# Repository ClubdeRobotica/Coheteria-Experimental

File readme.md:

# Vectores experimentales

## Introducción:
Es un proyecto orientado principalmente al estudio de la construccion de cohetes para el lanzamiento de nano satelites. Como incio del proyecto lo que se busca es generar la tecnologia y documentacion necesaria para poder realizar lanzamientos de cansat ( un pequeño satélite del tamaño de una lata de gaseosa). Por otro lado se busca generar mayor interes en las actividades espaciales que son muy pocas difundidas y asi ayudar con el progreso tecnológico.

## Objetivos

El objetivo principal de este proyecto, es lograr desarrollar un pequeño lanzador, que se pueda replicar facilmente y que sea capaz de llevar un cansat a una altura de unos 500 a 1000 metros.
Dividimos al proyecto en dos fases principales, con la primera nos planteamos generar todas las herramientas necesarias para el desarrollo de cohetes, y en la segunda se comienza a desarrollar cohetes y motores.
Dado que este proyecto está apuntado a ser desarrollado por estudiantes sin niguna experiencia previa en coheteria, se planea generar un entorno de desarrollo completo, para que sea posible evaluar los dferentes diseños, tanto de motores como de cohetes.

## Primera Fase
Para poder resolver todos los problemas que surjan a la hora de armar y lanzar un cohete desde cero, se plantean dos bloques de telemetria:
- Kit de Desarrollo de Motores, compuesto por:
 - Un kit de desarrollo para motores de azucar, que permita medir el empuje generado por las distintos propelentes, para poder experimentar con distintos motores sin necesidad de tener que ir al campo a probarlo en un cohete.
 - Una estacion terrena para el controlador de vuelo, es un software que se conecta al controlador de vuelo y permite descargar todos los datos almacenados durante el vuelo y generar graficos que permitan visualizar mas clararamente los datos.
- Kit de Desarrollo para Cohetes, compuesto por:
 - Controlador de vuelo electrónico, capaz de adquirir todos los datos del vuelo y guardarlos en una memoria para su posterior análisis.
 - Una estacion de control para el banco de pruebas, se trata simplemente de un software capaz de conectarse al banco y desde el cual se puedan visualizar todos los datos generados durante la prueba.

Como un anexo para esta fase, se añade el desarrollo de una plataforma para el lanzamiento de los cohetes.

### Kit de Desarrollo de Motores

El kit de desarrollo para motores de baja potencia, esta compuesto por un sistema mecanico donde se montan los motores y la electrónica necesaria para el analisis del empuje y un sistema informatico para controlar las pruebas. Este kit se encuentra en la etapa final del desarrollo y se puede ver en la [pagina del banco de pruebas](https://github.com/ClubdeRobotica/Coheteria-Experimental/tree/Bayo_V1/Motor/Banco%20de%20pruebas)

#### Sistema mecánico
El sistema mecánico, fabricado con perfiles de aluminio es simplemente una plataforma deslizante y un montaje para una celda de carga. La electronica implicada en este banco es la mas sencilla puesto que se trata simplemente de una placa Wemos D1, con un firmware de arduino que nos permite activar un relay para encender el motor y tomar mediciones de la celda de carga por WiFi.

#### Sistema informático
Está desarrollado en python y ademas de conectarse al banco de pruebas, nos muestra un grafico sencillo de empuje/tiempo.

### Kit de Desarrollo de Cohetes

Se trata como se dijo antes de una placa de telemetria que durante el vuelo va tomando a intervalos regulares, mediciones de presión, temperatura y aceleración y almacenandolos en un archivo que al finalizar el vuelo se puede descargar para su analisis. Adicionalmente se agrega un buzzer, que previo al despegue idica los distintos estados del sistema por medio de distintas combinaciones sonoras y al final del mismo, genera una alarma para facilitar su recuperacion en caso de caer en terreno accidentado.

#### Sistema Electrónico
La placa esta basada en un ESP8266 (en una primera fase en Wemos D1 mini, para simplificar el desarrollo) con un firmware de tiempo real basado en freeRTOS.
Consta de:
- Placa principal: Wemos D1 mini, modificada para mayor alcance del WiFi.
- Sensor de presion y temperatura BMP180
- Acelerómetro de tres ejes ADXL345
- Buzzer
- Bateria de 3.6V

Al iniciar, activa un AP WiFi y un servidor web al que se puede acceder desde una pc, para configurar las condiciones iniciales, o activar el modo de vuelo. Una vez activado el modo de vuelo, el sistema apaga el AP y queda a la espera del despegue, que es detectado por medio de los acelerometros. Una vez iniciado el vuelo, se toman mediciones a intervalos regulares programables de 10, 50, 100 o 500 ms segun se haya configurado y se almacenan los datos en un archivo. Luego de transcurridos un segundo sin detectar variaciones en los sensores, se supone que se ha tocado tierra nuevamente, se detienen las mediciones y se inicia el modo recuperación en el cual se activa nuevamente el AP y se hace sonar el buzzer.

#### Sistema Informatico
Es un software desarrollado en Python, que permite controlar tanto la plataforma de lanzamiento para iniciar el vuelo como graficar los datos del vuelo para su visualizacion.

## Estructura del repo:

## Como Participar
Buena parte del desarrollo del proyecto, puede hacerse de manera remota, por lo que no es necesario estar presente en las reuiones de trabajo.
Para participar se puede enviar un correo electrónico a cualquiera de los administradores del proyecto, o por medio del formulario de contacto de la pagina del [Club de Robótica](https://clubderobotica.github.io/).

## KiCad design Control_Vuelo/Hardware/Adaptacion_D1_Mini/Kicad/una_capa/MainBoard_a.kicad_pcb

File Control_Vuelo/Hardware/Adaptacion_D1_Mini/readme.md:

# Controlador de Vuelo

## PCB Adaptacion Wemos D1 Mini

 El primer objetivo de este pcb es tener una placa madre que contenga los sensores de presion y temperatura, acelerometros, conector para la bateria y buzzer.
 En esta primera version, para simplificar el desarrollo del firmware se armara un shield para el Wemos D1 Mini que quepa en el interior de un tubo de 50mm. De este modo, se puede ir probando el firmware con una protoboard y un Wemos D1 que sabemos que funciona bien.
 Caracteristicas del shield:
-  	 Conector para Wemos D1 Mini
-  	 Conector para Baterias
-  	 Acelerometro lineals de 3 ejes
-  	 Multiplexor analogico para seleccion del acelerometro
-  	 Sensor de presion y temperatura
-  	 Buzzer
 
## PCB ESP8266

 Una segunda version de la misma placa, integra en el PCB del mainboard el modulo ESP-07 y un header para conectar un puerto serie, mas el boton de reset y un jumper que permita bootear el esp8266 en modo flash.
 En esta version, se eliminan conectores y el Wemos D1, disminuyendo el peso total del controlador.
 Caracteristicas de la placa:
-  	 Conector para puerto serie
-  	 Switch Reset
-  	 Jumper de seleccion de modo de booteo
-  	 ESP8266 con conector para antena externa
-  	 Conector para Baterias
-  	 Acelerometro lineals de 3 ejes
-  	 Multiplexor analogico para seleccion del acelerometro
-  	 Sensor de presion y temperatura
-  	 Buzzer

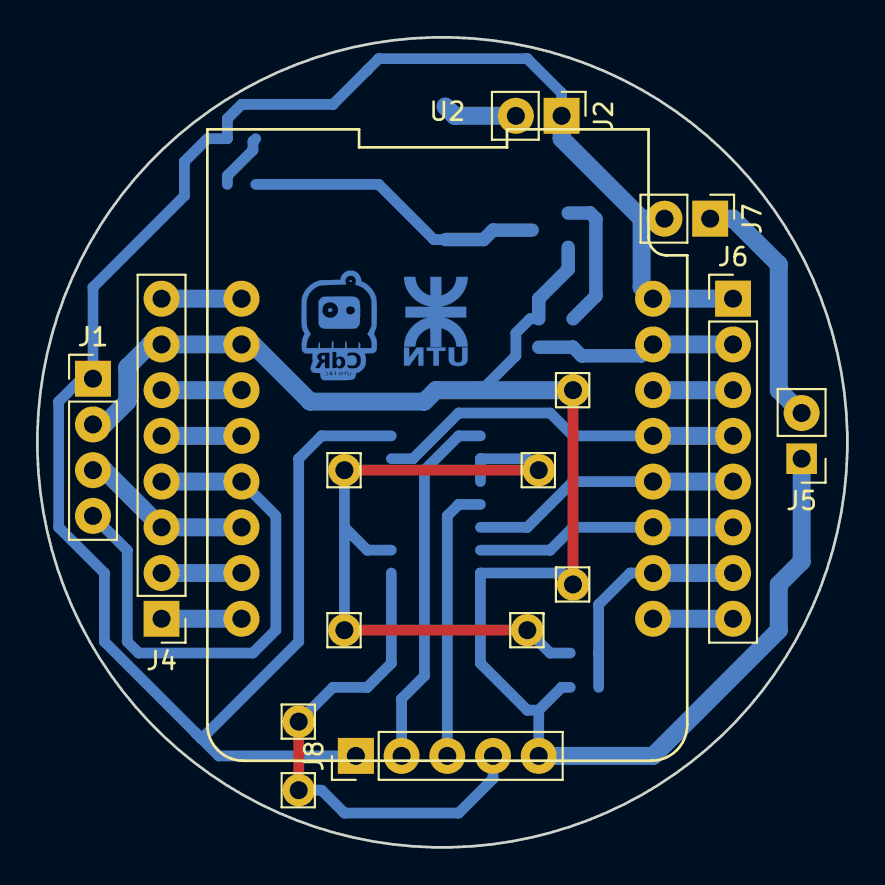
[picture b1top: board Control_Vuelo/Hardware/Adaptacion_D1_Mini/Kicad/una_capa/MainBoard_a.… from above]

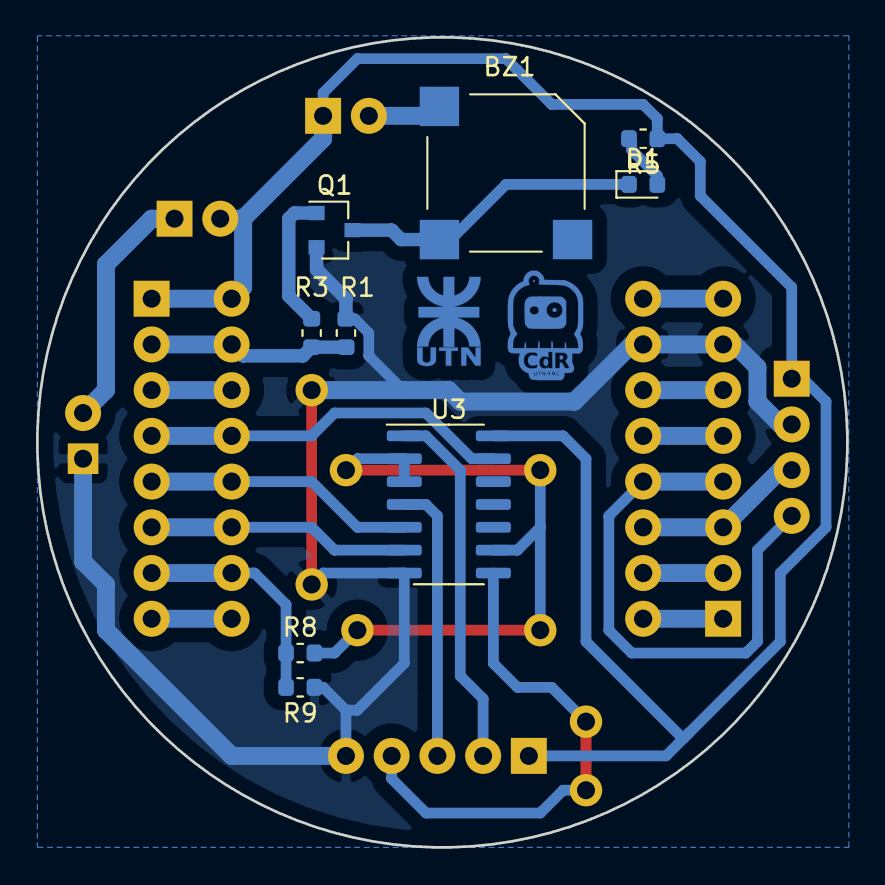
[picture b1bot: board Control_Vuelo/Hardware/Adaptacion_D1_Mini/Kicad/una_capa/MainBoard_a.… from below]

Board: 2 copper layers, 45.0 x 45.0 mm, 17 parts (9 on the bottom side), 25 nets.

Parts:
BZ1: Buzzer; MagneticBuzzer_Kobitone_254-EMB84Q-RO
D1: LED; LED_0603_1608Metric
J1: Conn_01x04; PinHeader_1x04_P2.54mm_Vertical
J2: Desabilitar buzzer; PinHeader_1x02_P2.54mm_Vertical
J4, J6: Conn_01x08; PinHeader_1x08_P2.54mm_Vertical
J5: Bateria; PinHeader_1x02_P2.54mm_Vertical
J7: Llave; PinHeader_1x02_P2.54mm_Vertical
J8: Conn_01x05; PinHeader_1x05_P2.54mm_Vertical
Q1: BC817; SOT-23
R1, R3, R5, R9: 10k; R_0603_1608Metric
R8: 220k; R_0603_1608Metric
U2: WeMos_mini; wemos-d1-mini-with-pin-header-and-connector
U3: 4066; SOIC-14_3.9x8.7mm_P1.27mm

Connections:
3v3: J1.1, J2.1, J6.1, J7.2, J8.1, R5.1, U2.8, U3.14
Analog: J6.7, R8.1, R9.2, U2.2
Buzzer: J6.2, R1.2, R3.2, U2.7
D0_pgm: J4.5, U2.12
D7: J6.3, U2.6
G2: J4.6, U2.11
GND: J1.2, J4.7, J5.1, J8.5, Q1.2, R1.1, R9.1, U2.10, U3.7
unnamed: J5.2, J7.1
unnamed: BZ1.1, J2.2
unnamed: BZ1.2, D1.1, Q1.3
unnamed: D1.2, R5.2
unnamed: J4.8, U2.9
unnamed: J8.2, U3.1
unnamed: J8.3, U3.4
unnamed: J8.4, U3.8
unnamed: Q1.1, R3.1
unnamed: R8.2, U3.2, U3.3, U3.9
RST: J6.8, U2.1
SCL: J1.3, J4.3, U2.14
SDA: J1.4, J4.4, U2.13
UART-Rx: J4.1, U2.16
UART-Tx: J4.2, U2.15
X_Sel: J6.6, U2.3, U3.6
Y_Sel: J6.5, U2.4, U3.5
Z_Sel: J6.4, U2.5, U3.13

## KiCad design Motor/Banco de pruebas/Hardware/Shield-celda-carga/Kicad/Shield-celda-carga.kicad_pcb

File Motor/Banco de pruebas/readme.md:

# Banco de pruebas

El objetivo de este bloque es desarrollar un banco de pruebas de bajo coste y fácil de replicar, que pueda ser replicado por cualquiera sin necesidad de muchos conocimientos de electrónica. Permitiendo poner toda la atención en el desarrollo de motores.

En la imagen se muestra un boceto de la estructura mecanica del banco, se trata de un sistema de rieles con un soporte para fijar el motor y una celda de carga en uno de sus extremos para tomar el valor de la fuerza instantanea generada por el motor.

El conectarlo a la energia, el banco monta una red WiFi a la cual se puede acceder desde cualquier PC. Una vez conectado a la red se ejecuta el software de adquisición de datos desde el que se puede controlar la ignicion del motor y se visualizan los datos en tiempo real.

## Software
El software de adquisicion esta programado en python y es multiplataforma, sólo requiere tener python instalado para correr.

## Placa electrónica

La electrónica del banco esta basada en la placa Weemos D1 que integra un modulo WiFi ESP8266 dentro de una placa de desarrollo con formato de Arduino UNO. Se agrega un shield con un relé que controla la ignición del motor y un conector para el conversor A/D HX711.

### Estado

En el video se muetra una prueba del banco y los datos de fuerza y tiempo en tiempo real, los datos son guardados en un archivo de tipo CSV.

#### Para agregar
##### Software:
* Se cuelga si al hacer clic en iniciiar la pc no esta conectada al banco.
* Falta agregar una opcion que permita seleccionar la ruta y el nombre del archivo csv donde se guardan los datos.

##### Firmware:
* Se deberia agregar una opcion de calibracion.
* Deberia poder determinar el fin de la prueba y dejar de enviar datos.

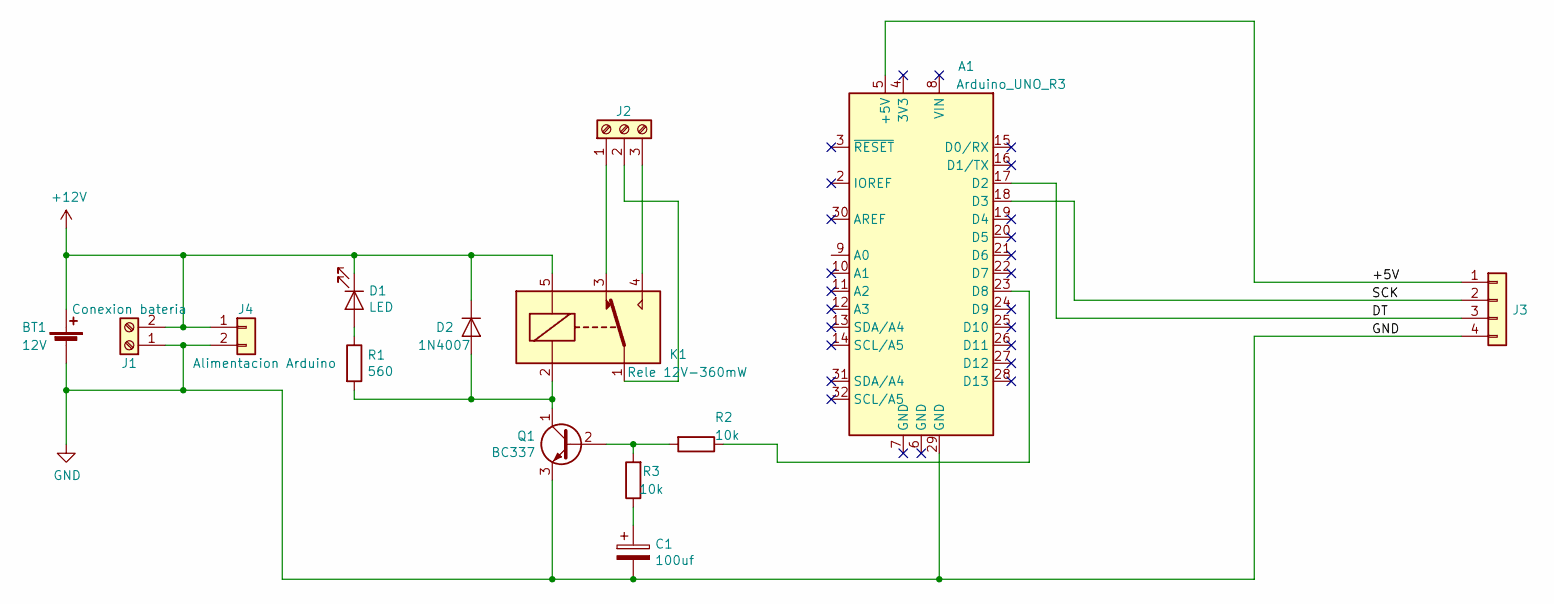
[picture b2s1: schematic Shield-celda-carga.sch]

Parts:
A1: Arduino_UNO_R3
BT1: 12V
C1: 100uf; CP_Radial_D6.3mm_P2.50mm
D1: LED; LED_D5.0mm
D2: 1N4007; D_DO-41_SOD81_P10.16mm_Horizontal
J1: Conexion bateria; Altech_AK300_1x02_P5.00mm_45-Degree
J2: Screw_Terminal_01x03; Altech_AK300_1x03_P5.00mm_45-Degree
J3: Conn_01x04; PinHeader_1x04_P2.54mm_Horizontal
J4: Alimentacion Arduino; PinHeader_1x02_P2.54mm_Vertical
K1: Rele 12V-360mW; Relay_HF7FD
Q1: BC337; TO-92L_Wide
R1: 560; R_Axial_DIN0207_L6.3mm_D2.5mm_P7.62mm_Horizontal
R2, R3: 10k; R_Axial_DIN0207_L6.3mm_D2.5mm_P7.62mm_Horizontal

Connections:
+12V: BT1.1 (+), D1.1 (K), D2.1 (K), J1.2, J4.1, K1.5
/+5V: A1.5 (+5V), J3.1
/DT: A1.17 (D2), J3.3
/SCK: A1.18 (D3), J3.2
GND: A1.29 (GND), BT1.2 (-), C1.2, J1.1, J3.4, J4.2, Q1.3 (E)
unnamed: A1.23 (D8), R2.1
unnamed: C1.1, R3.1
unnamed: D1.2 (A), R1.1
unnamed: D2.2 (A), K1.2, Q1.1 (C), R1.2
unnamed: J2.1, K1.3
unnamed: J2.2, K1.1
unnamed: J2.3, K1.4
unnamed: Q1.2 (B), R2.2, R3.2

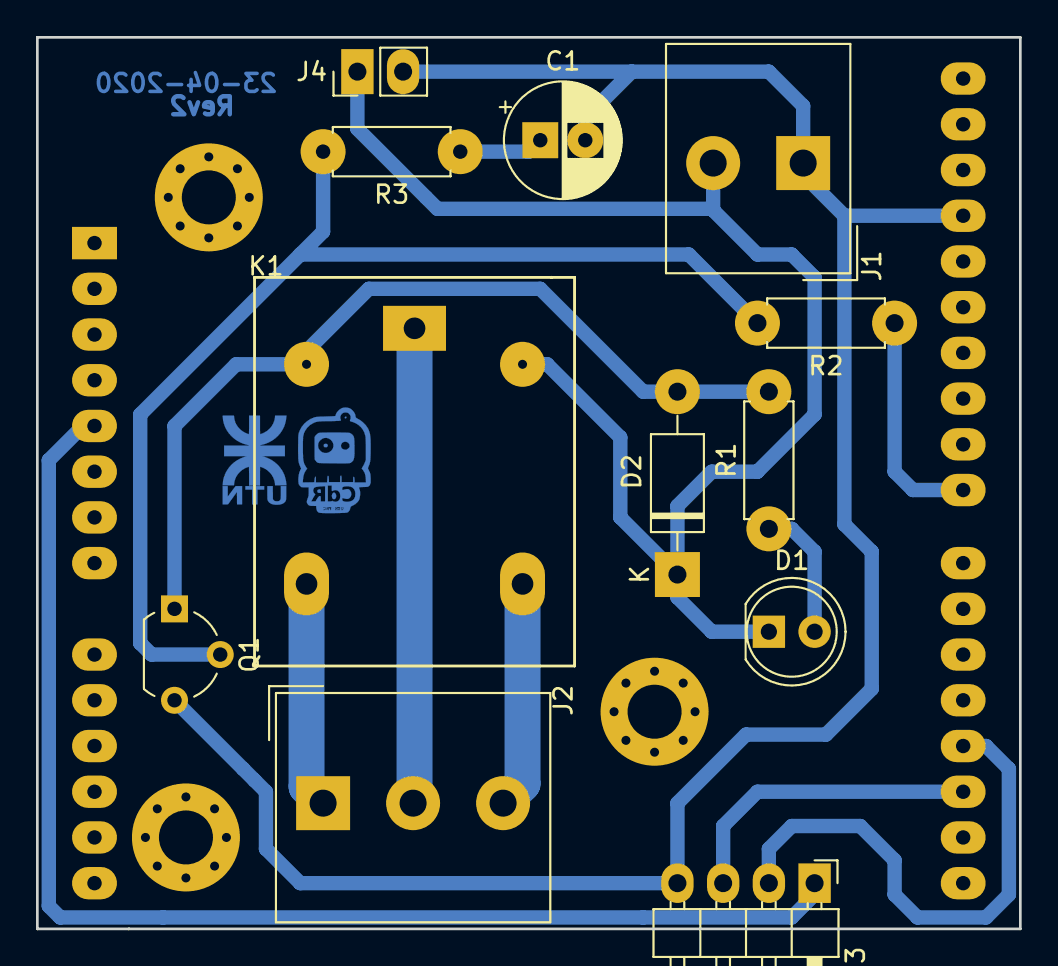
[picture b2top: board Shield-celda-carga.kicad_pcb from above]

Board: 2 copper layers, 54.6 x 49.5 mm, 13 parts (1 on the bottom side), 13 nets.

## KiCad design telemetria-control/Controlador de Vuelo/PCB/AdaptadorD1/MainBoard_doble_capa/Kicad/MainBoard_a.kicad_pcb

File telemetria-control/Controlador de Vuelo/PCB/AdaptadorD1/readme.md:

# Adaptador D1

## PCB Adaptacion Wemos D1 Mini

 El objetivo de este pcb es poder conectar una placa de desarrollo wemos mini D1 a las placas de sensores que se van a colocar en los cohetes.
 Debe ser un shield con pines hembra en el medio para conectar el D1 Mini y en el exterior pines macho para conectar las placas de sensores como esta en la imagen PCBSensores.png, los conectores 1 y 2 son van se conectan al conector de la izquierda del mini d1 y los conectores 3 y 4 al de la derecha

## PCB Sensor Presion

 Un PCB del mismo tamano que el otro algo similar a la imagen, el espacio da justo para poner un sensor BMP180 (1) y el conector para la bateria (2). Lo ideal es que tenga las cuatro tiras de pines a los costados, pero se puede aliminar alguno en caso de que falte espacio.
 Lo unico a tener en cuenta es que ademas de la alimentacion, los pines SDA y SCL tiene que ir conectados con los pines D2 y D1 del Wemos.
 D2 -- SDA
 D1 -- SCL

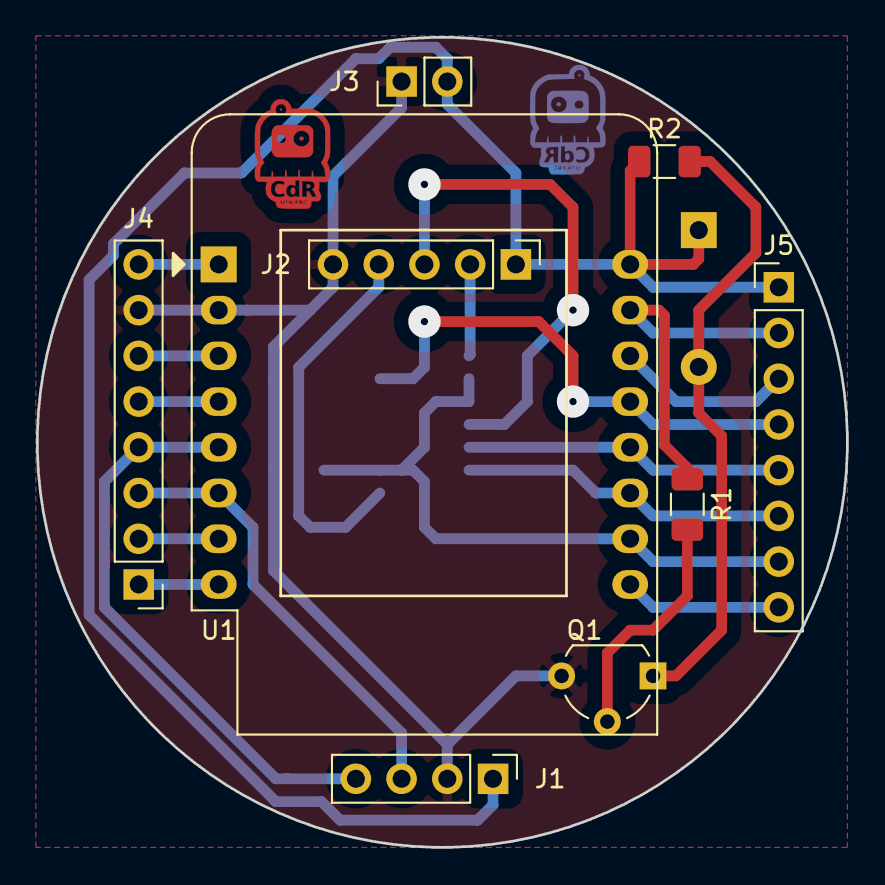
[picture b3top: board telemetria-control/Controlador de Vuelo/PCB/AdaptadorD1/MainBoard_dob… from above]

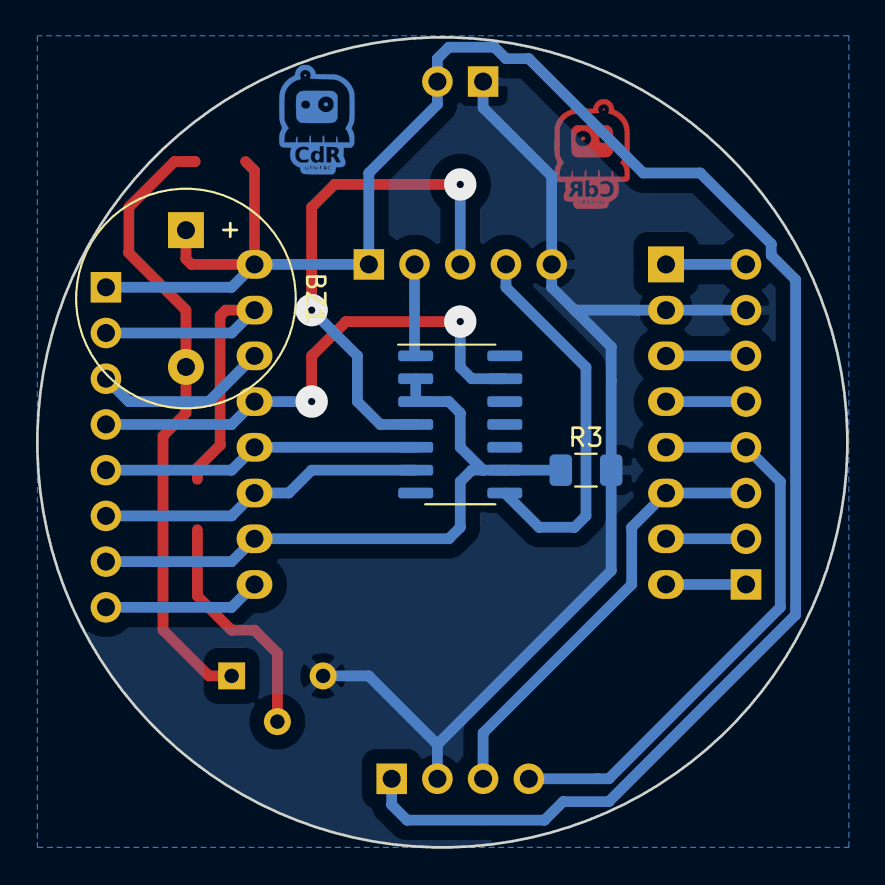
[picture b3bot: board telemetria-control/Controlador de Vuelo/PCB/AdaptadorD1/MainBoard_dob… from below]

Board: 2 copper layers, 45.0 x 45.0 mm, 12 parts (3 on the bottom side), 21 nets.

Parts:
BZ1: Buzzer; Buzzer_12x9.5RM7.6
J1: Conn_01x04; PinHeader_1x04_P2.54mm_Vertical
J2: Conn_01x05; PinHeader_1x05_P2.54mm_Vertical
J3: Conn_01x02; PinHeader_1x02_P2.54mm_Vertical
J4, J5: Conn_01x08; PinHeader_1x08_P2.54mm_Vertical
Q1: BC548; TO-92L_Wide
R1, R2: 10k; R_1206_3216Metric
R3: 10K; R_1206_3216Metric
U1: WeMos_mini; WEMOS_D1_mini_light
U2: 4066; SOIC-14_3.9x8.7mm_P1.27mm

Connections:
3v3: BZ1.1, J1.1, J2.1, J3.2, J5.1, R2.1, U1.16
Analog: J5.7, R3.1, U1.10, U2.2, U2.3, U2.9
Buzzer: J5.2, R1.2, U1.15
GND: J1.2, J2.5, J3.1, J4.7, Q1.3, R3.2, U1.2
unnamed: BZ1.2, Q1.1, R2.2
unnamed: J2.2, U2.1
unnamed: J2.3, U2.4
unnamed: J2.4, U2.8
unnamed: J4.1, U1.8
unnamed: J4.2, U1.7
unnamed: J4.5, U1.4
unnamed: J4.6, U1.3
unnamed: J4.8, U1.1
unnamed: J5.3, U1.14
unnamed: J5.8, U1.9
unnamed: Q1.2, R1.1
SCL: J1.3, J4.3, U1.6
SDA: J1.4, J4.4, U1.5
X_Sel: J5.6, U1.11, U2.6
Y_Sel: J5.5, U1.12, U2.5
Z_Sel: J5.4, U1.13, U2.13

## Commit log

2018-03-26 Primer Commit
2018-03-26 Primer Commit readme.md
2018-03-26 Formateo readme.md
2018-03-26 Estructura Repositorio
2018-03-26 Mas archivos readme.md
2018-04-20 Subo minuta primer reunion
2018-04-22 Agrego algo de estructura para el proyecto
2018-04-27 prueba commit
2018-04-28 nombre sin espacios
2018-04-28 boceto de especificaciones
2018-04-29 algo de info
2018-04-30 Agrego info sobre protocolos
2018-04-30 Agrego algo de info sobre CANbus
2018-05-01 agregado de ejemplo de lectura de 3 ADC para arduino UNO
2018-05-01 Hojas de datos necesarios
2018-05-06 agrego prototipos de funciones que faltan hacer
2018-05-12 PCB nucleo
2018-05-12 readme pcb
2018-05-13 primer version del prototipo
2018-05-15 esquemático modificado
2018-05-18 agregados capacitores de desacople
2018-06-05 Abstract del proyecto
2018-06-05 Avance del proyecto
2018-06-06 Software del banco de pruebas
2018-06-10 avance del proyecto primera
2018-06-10 avance del proyecto 10-06
2018-06-18 agrego modelo del banco al estado de proyecto
2018-06-21 agrego componentes smd en la netlist
2018-06-21 modelo simple para cansat
2018-08-22 Correcciones en el readme.md
2019-01-13 Agregado un proyecto de base para desarrollar el firmware en eclipse con RTOS
2019-01-13 readme.md con info sobre como subir
2019-01-13 Correcciones al readme.md de firmware
2019-02-11 primer test, blinky y eco por puerto serie
2019-03-24 Primer proyecto de testeo uart y gpioled
2019-03-24 Ejempo de i2c hecho para un mpu, hay que ir modificando para el bmp180
2019-03-29 Ejemplos socket
2019-03-29 software principal
2019-03-29 Noticias
2019-03-29 nucleo.net
2019-03-30 Base de datos
2019-03-30 Version 1.0
2019-03-30 Nuevo
2019-03-31 Agrega wifi al firmware
2019-04-02 agrego trama json de ejemplo
2019-04-02 Arreglos
2019-04-02 Ejemplo de lectura
2019-04-13 Vuelvo a version alfa
2019-04-17 version de test con ide de arduino
2019-04-17 elimino un poco de texto del debug por puerto serie
2019-04-18 agrego ultimas modificaciones
2019-04-19 Se copio data para procesar
2019-04-19 Se arreglo el bug por perdida de comunicacion
2019-04-19 Nueva version de ET con mas funciones
2019-04-19 se borraron los datos
2019-04-27 restore
2019-05-11 agrego requisitos conector para el wemos d1 mini
2019-05-11 agrego imagen pcb sensores
2019-05-11 agrego requerimentos de la placa
2019-05-23 wifi
2019-07-08 Primera Version del firmware del banco de pruebas
2019-07-21 Actualizacion del readme
2019-07-22 Nuevo software del banco
2019-07-22 Se quitaron variables globales
2019-07-22 Se agrego respuesta del soft al controlador de vuelo
2019-07-22 Preba brach
2019-07-22 Preba master
2019-07-22 Prueba 2
2019-07-22 Prueba 3
2019-07-22 Pruea 4
2019-07-22 Arreglo listo
2019-07-22 Archivo de borrable
2019-07-22 se saco archivo innecesario
2019-07-24 agrego sockets
2019-07-24 no se clava si no recibe datos
2019-07-24 arreglos com y banco
2019-07-24 arreglos de ejes
2019-07-24 Error en linea 23
2019-07-24 Primer version probada con el soft
2019-07-24 pasa a newton
2019-07-25 Ahora el ip se agrega en las configuraciones
2019-07-26 Primera version del shield, no encontre relays en kicad, puse un opto
2019-07-26 imagenes del soft para la wiki
2019-07-26 Mejoras visuales
2019-09-26 Ahora todo funciona unicamente con python 3
2019-09-28 Soportes para los rodamientos y las guias
2019-09-29 soporte para la torre
2019-10-20 Estructura del firmware con RTOS, falta integrar
2019-10-20 Descripcion del firmware
2019-10-20 Tarea de control del barometro
2019-10-20 Primer version de la mainboard con bmp, bat y buzzer
2019-10-21 version para imprimir desde gimp
2019-10-24 agrego tarea de testeo del buzzer
2019-10-25 primer version del sistema de archivos
2019-11-02 separo modulos y agrego queues
2019-11-02 primer prototipo del controlador
2019-11-02 bloques p wiki
2019-11-02 pines wemos d1
2019-11-26 Esquematico version completa
2019-11-27 nueva descripcion
2020-03-29 se movio datos tecnicos de bateria y zumbador a la carpeta de hojas de datos
2020-03-29 Error: se hizo una placa nueva arriba del proyecto de una vieja, Solucion:se restauro la version mas vieja y se creo la placa nueva en otra carpeta
2020-03-29 se agrega la nueva placa en una nueva carpeta
2020-03-30 Se modificaron los tamaños de algunos pads en kicad y se reimprimieron los archivos de PCB
2020-04-05 Agregue placa en kicad de banco de pruebas, datasheet, vistas 3D y PCB
2020-04-06 reorganizando
2020-04-08 Reorganizando la estructura del repositorio
2020-04-08 Agrego descripicion controlador de vuelo
2020-04-08 Elimino archivos viejos
2020-04-08 Modifico descripcion
2020-04-09 siguiendo la reestructuracion
2020-04-09 se modifico un .md y se borro archivos no utiles en estacion terrena
2020-04-09 se modifico nombre de carpeta en /motor/hardware/banco de pruebas -> shield celda de carga
2020-04-09 se agrego diagrama de arbol de archivos en documentacion
2020-04-09 modificacion
2020-04-10 Nueva placa Shield-celda-carga
2020-04-11 pinout del shield
2020-04-15 modifico las configuraciones para que se conecte a una ip por defecto
2020-04-15 agrego para que active el rele cuando se inicia la prueba
2020-04-18 corrijo pinout para que funcione en el shield
2020-04-18 se modifico shiel-celda-carga la distribucion de pines
2020-04-18 se le agrego contorno a la placa PCB shield-celda-carga
2020-04-23 seagrego tira de pines hembras al PCB y se modificaron vistas 3D
2020-04-24 Se agrego un circuito RC en la base del transistor del rele por problemas de ruiido al resetear y se creo la Rev2
2020-04-24 se eliminaron archivos en el PCB de celda de carga de una version mas vieja
2020-04-25 Modificacion en la placa adaptacion_D1_mini en la pista de 3,3V
2020-04-25 Calibrando la balanza
2020-04-25 agrego filtrado de lecturas
2020-04-25 agrego gitignore para que ignorar archivos de salida
2020-04-25 los datos ahora tambien se guardan en un archivo de celdas
2020-06-18 Primer prueba de motor falla, ignicion
2020-06-19 Prueba motor C
2020-06-19 Prueba Motor C8-4
2020-06-21 Descripcion del banco
2020-06-22 Actualizacion del estado
2020-11-16 se dejo dos diseños de PCB en el hardware de sistema de vuelo, uno de doble capa y otro de capa simple
2020-11-16 Cambios en el 3D del Kicad, se genero vistas 3D y PCB para imprimir
2020-11-19 Se corrigio un problema de superposicion en el PCB y se agregaron los Gerber
